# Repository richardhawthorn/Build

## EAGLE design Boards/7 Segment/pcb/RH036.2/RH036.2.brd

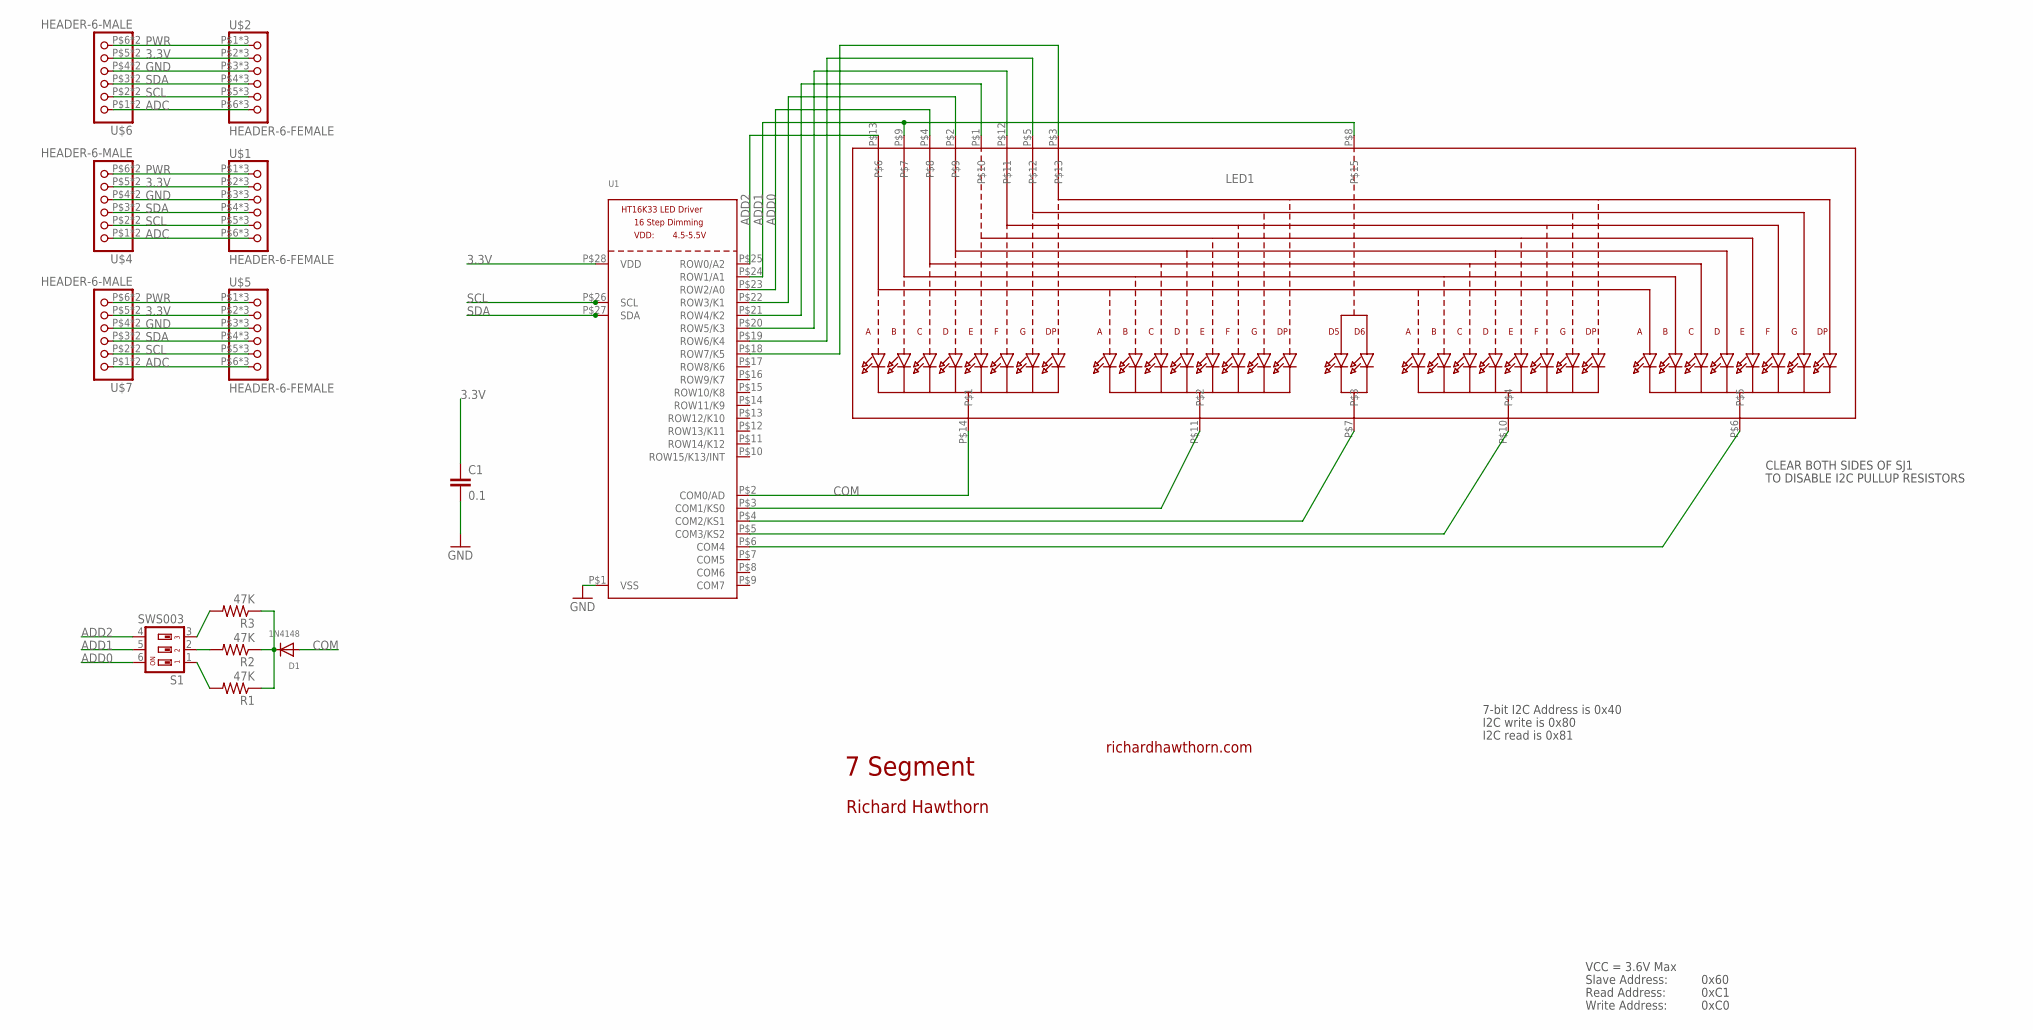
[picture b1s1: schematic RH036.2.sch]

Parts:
C1: 0.1; 0603-CAP
D1: 1N4148; SOD-323F
LED1: DISP_SEGMENT_4DIGIT_BL-Q56C43; SEGMENT-BL-Q56C43
R1, R2, R3: 47K; R0805
S1: SWS003; SMS-003
U1: HT16K33_SOP28; SOP28_300MIL
U$1, U$2, U$5: HEADER-6-FEMALE; 2MMHEADER6
U$4, U$6, U$7: HEADER-6-MALE; 2MMHEADERPIN6

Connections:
3.3V: C1.1, U1.P$28 (VDD), U$1.P$2 (2), U$1.P$10 (2), U$1.P$18 (2), U$2.P$2 (2), U$2.P$10 (2), U$2.P$18 (2), U$4.P$5 (5), U$4.P$13 (5), U$5.P$2 (2), U$5.P$10 (2), U$5.P$18 (2), U$6.P$5 (5), U$6.P$13 (5), U$7.P$5 (5), U$7.P$13 (5)
ADC: U$1.P$6 (6), U$1.P$14 (6), U$1.P$22 (6), U$2.P$6 (6), U$2.P$14 (6), U$2.P$22 (6), U$4.P$1 (1), U$4.P$9 (1), U$5.P$6 (6), U$5.P$14 (6), U$5.P$22 (6), U$6.P$1 (1), U$6.P$9 (1), U$7.P$1 (1), U$7.P$9 (1)
ADD0: LED1.P$4, S1.6, U1.P$23 (ROW2/A0)
ADD1: LED1.P$8, LED1.P$9, S1.5, U1.P$24 (ROW1/A1)
ADD2: LED1.P$13, S1.4, U1.P$25 (ROW0/A2)
COM: D1.A, LED1.P$14, U1.P$2 (COM0/AD)
GND: C1.2, U1.P$1 (VSS), U$1.P$3 (3), U$1.P$11 (3), U$1.P$19 (3), U$2.P$3 (3), U$2.P$11 (3), U$2.P$19 (3), U$4.P$4 (4), U$4.P$12 (4), U$5.P$3 (3), U$5.P$11 (3), U$5.P$19 (3), U$6.P$4 (4), U$6.P$12 (4), U$7.P$4 (4), U$7.P$12 (4)
unnamed: R3.2, S1.3
unnamed: LED1.P$11, U1.P$3 (COM1/KS0)
unnamed: LED1.P$7, U1.P$4 (COM2/KS1)
unnamed: LED1.P$10, U1.P$5 (COM3/KS2)
unnamed: LED1.P$6, U1.P$6 (COM4)
unnamed: LED1.P$2, U1.P$22 (ROW3/K1)
unnamed: LED1.P$1, U1.P$21 (ROW4/K2)
unnamed: LED1.P$12, U1.P$20 (ROW5/K3)
unnamed: LED1.P$5, U1.P$19 (ROW6/K4)
unnamed: LED1.P$3, U1.P$18 (ROW7/K5)
unnamed: D1.C, R1.1, R2.1, R3.1
unnamed: R1.2, S1.1
unnamed: R2.2, S1.2
PWR: U$1.P$1 (1), U$1.P$9 (1), U$1.P$17 (1), U$2.P$1 (1), U$2.P$9 (1), U$2.P$17 (1), U$4.P$6 (6), U$4.P$14 (6), U$5.P$1 (1), U$5.P$9 (1), U$5.P$17 (1), U$6.P$6 (6), U$6.P$14 (6), U$7.P$6 (6), U$7.P$14 (6)
SCL: U1.P$26 (SCL), U$1.P$5 (5), U$1.P$13 (5), U$1.P$21 (5), U$2.P$5 (5), U$2.P$13 (5), U$2.P$21 (5), U$4.P$2 (2), U$4.P$10 (2), U$5.P$5 (5), U$5.P$13 (5), U$5.P$21 (5), U$6.P$2 (2), U$6.P$10 (2), U$7.P$2 (2), U$7.P$10 (2)
SDA: U1.P$27 (SDA), U$1.P$4 (4), U$1.P$12 (4), U$1.P$20 (4), U$2.P$4 (4), U$2.P$12 (4), U$2.P$20 (4), U$4.P$3 (3), U$4.P$11 (3), U$5.P$4 (4), U$5.P$12 (4), U$5.P$20 (4), U$6.P$3 (3), U$6.P$11 (3), U$7.P$3 (3), U$7.P$11 (3)

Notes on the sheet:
7 Segment
richardhawthorn.com
Richard Hawthorn
CLEAR BOTH SIDES OF SJ1
TO DISABLE I2C PULLUP RESISTORS
7-bit I2C Address is 0x40
I2C write is 0x80
I2C read is 0x81
VCC = 3.6V Max
Read Address:
Write Address:
Slave Address:
0x60
0xC1
0xC0

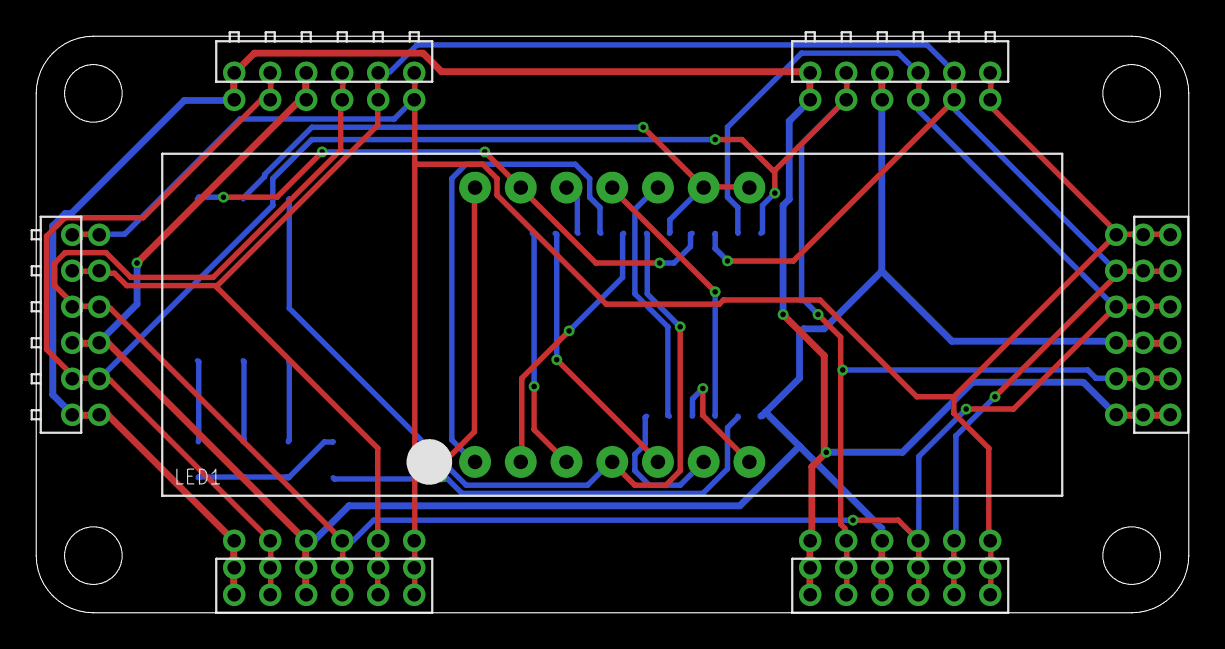
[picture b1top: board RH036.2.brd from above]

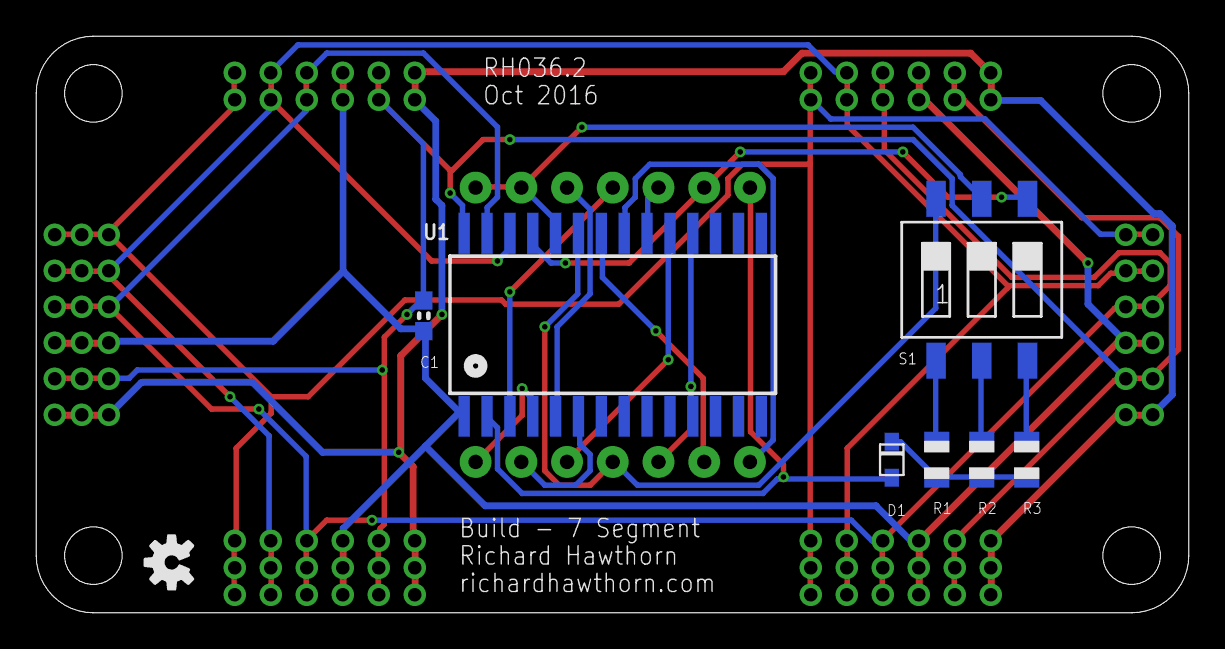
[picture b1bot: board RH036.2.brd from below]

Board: 2 copper layers, 64.0 x 32.0 mm, 15 parts (8 on the bottom side), 23 nets.

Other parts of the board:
U$3: OSHW-LOGO-S

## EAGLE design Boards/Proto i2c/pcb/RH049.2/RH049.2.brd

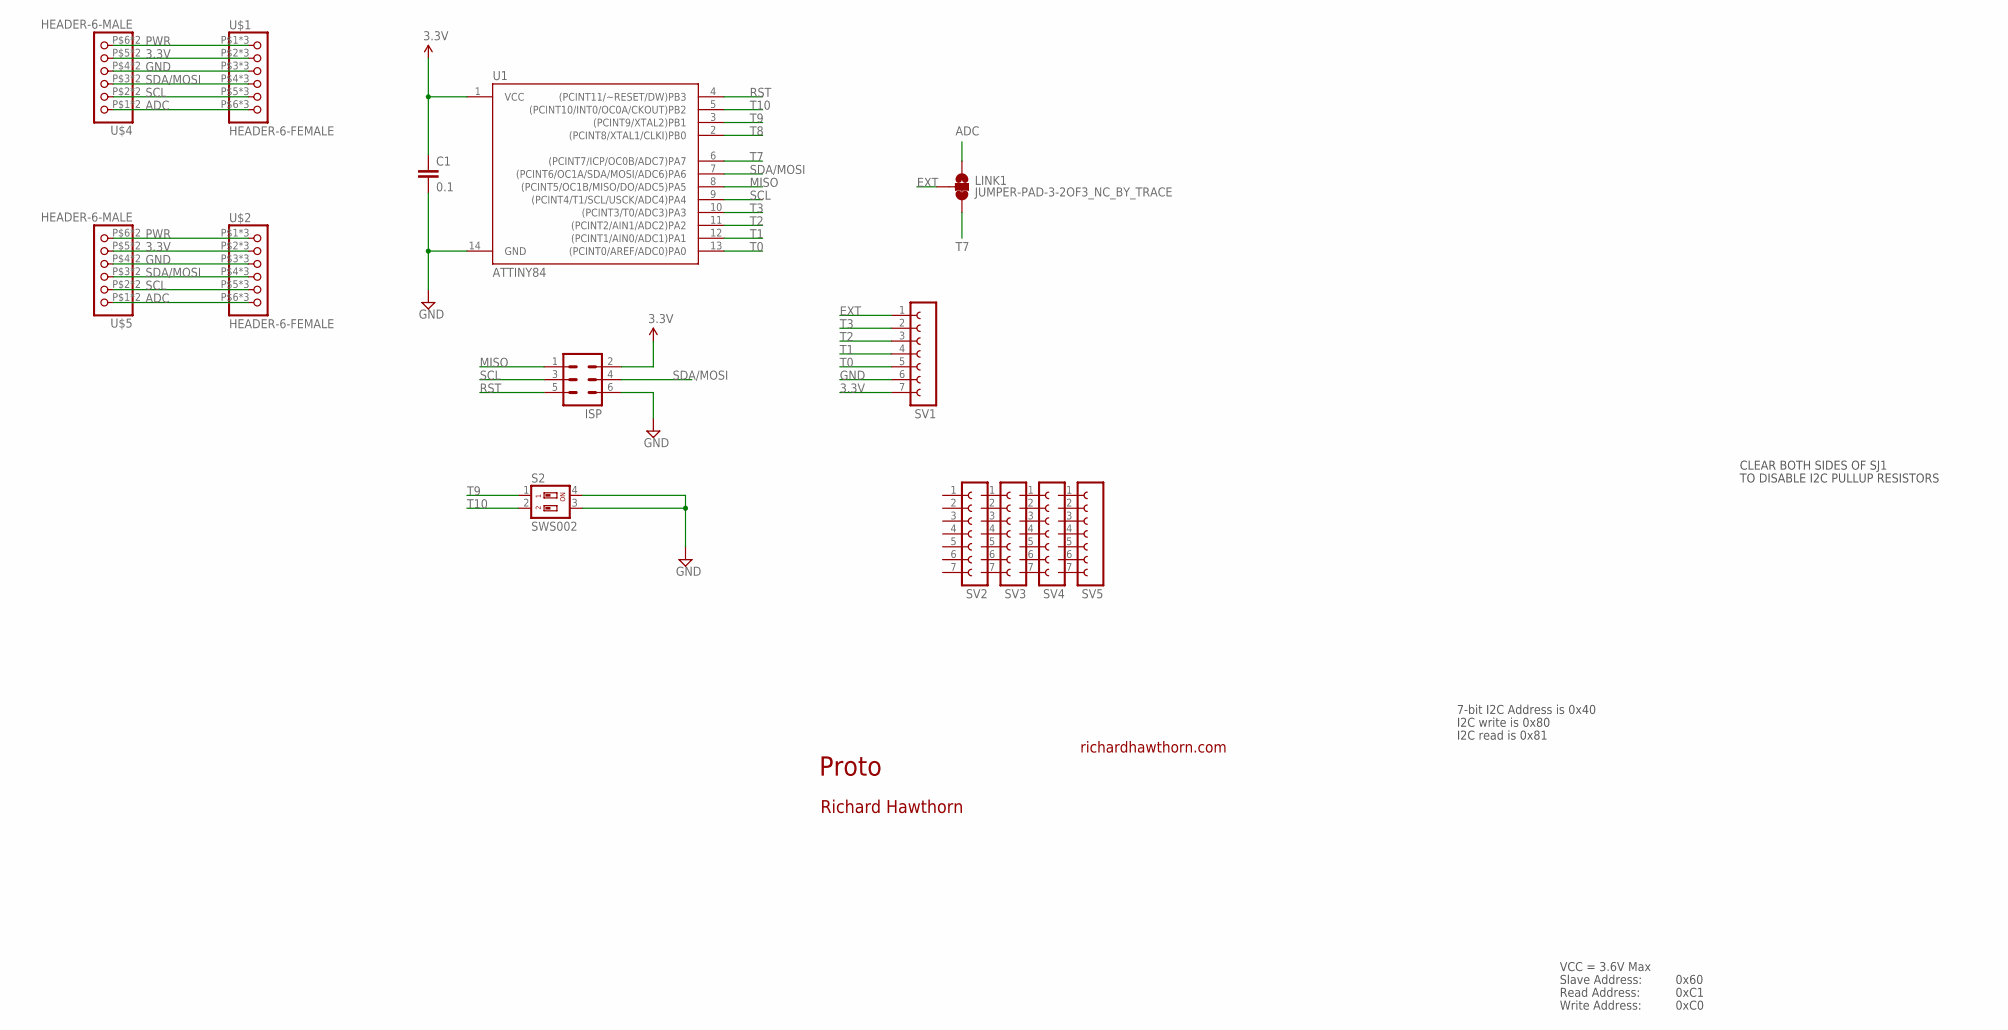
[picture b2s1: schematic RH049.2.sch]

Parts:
C1: 0.1; 0603-CAP
ISP: MA03-2
LINK1: JUMPER-PAD-3-2OF3_NC_BY_TRACE; PAD-JUMPER-3-2OF3_NC_BY_TRACE_YES_SILK_FULL_BOX
S2: SWS002; SMS-002
SV1, SV2, SV3, SV4, SV5: FE07-1; FE07
U1: ATTINY84; SO14
U$1, U$2: HEADER-6-FEMALE; 2MMHEADER6
U$4, U$5: HEADER-6-MALE; 2MMHEADERPIN6

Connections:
3.3V: C1.1, ISP.2, SV1.7, U1.1 (VCC), U$1.P$2 (2), U$1.P$10 (2), U$1.P$18 (2), U$2.P$2 (2), U$2.P$10 (2), U$2.P$18 (2), U$4.P$5 (5), U$4.P$13 (5), U$5.P$5 (5), U$5.P$13 (5)
ADC: LINK1.1, U$1.P$6 (6), U$1.P$14 (6), U$1.P$22 (6), U$2.P$6 (6), U$2.P$14 (6), U$2.P$22 (6), U$4.P$1 (1), U$4.P$9 (1), U$5.P$1 (1), U$5.P$9 (1)
EXT: LINK1.2, SV1.1
GND: C1.2, ISP.6, S2.3, S2.4, SV1.6, U1.14 (GND), U$1.P$3 (3), U$1.P$11 (3), U$1.P$19 (3), U$2.P$3 (3), U$2.P$11 (3), U$2.P$19 (3), U$4.P$4 (4), U$4.P$12 (4), U$5.P$4 (4), U$5.P$12 (4)
MISO: ISP.1, U1.8 ((PCINT5/OC1B/MISO/DO/ADC5)PA5)
PWR: U$1.P$1 (1), U$1.P$9 (1), U$1.P$17 (1), U$2.P$1 (1), U$2.P$9 (1), U$2.P$17 (1), U$4.P$6 (6), U$4.P$14 (6), U$5.P$6 (6), U$5.P$14 (6)
RST: ISP.5, U1.4 ((PCINT11/~RESET/DW)PB3)
SCL: ISP.3, U1.9 ((PCINT4/T1/SCL/USCK/ADC4)PA4), U$1.P$5 (5), U$1.P$13 (5), U$1.P$21 (5), U$2.P$5 (5), U$2.P$13 (5), U$2.P$21 (5), U$4.P$2 (2), U$4.P$10 (2), U$5.P$2 (2), U$5.P$10 (2)
SDA/MOSI: ISP.4, U1.7 ((PCINT6/OC1A/SDA/MOSI/ADC6)PA6), U$1.P$4 (4), U$1.P$12 (4), U$1.P$20 (4), U$2.P$4 (4), U$2.P$12 (4), U$2.P$20 (4), U$4.P$3 (3), U$4.P$11 (3), U$5.P$3 (3), U$5.P$11 (3)
T0: SV1.5, U1.13 ((PCINT0/AREF/ADC0)PA0)
T1: SV1.4, U1.12 ((PCINT1/AIN0/ADC1)PA1)
T2: SV1.3, U1.11 ((PCINT2/AIN1/ADC2)PA2)
T3: SV1.2, U1.10 ((PCINT3/T0/ADC3)PA3)
T7: LINK1.3, U1.6 ((PCINT7/ICP/OC0B/ADC7)PA7)
T8: U1.2 ((PCINT8/XTAL1/CLKI)PB0)
T9: S2.1, U1.3 ((PCINT9/XTAL2)PB1)
T10: S2.2, U1.5 ((PCINT10/INT0/OC0A/CKOUT)PB2)

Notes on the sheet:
Proto
richardhawthorn.com
Richard Hawthorn
CLEAR BOTH SIDES OF SJ1
TO DISABLE I2C PULLUP RESISTORS
7-bit I2C Address is 0x40
I2C write is 0x80
I2C read is 0x81
VCC = 3.6V Max
Read Address:
Write Address:
Slave Address:
0x60
0xC1
0xC0

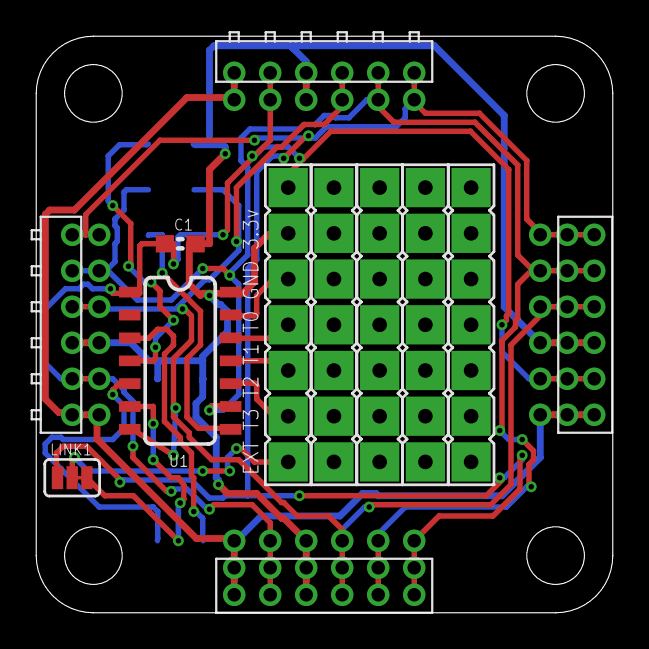
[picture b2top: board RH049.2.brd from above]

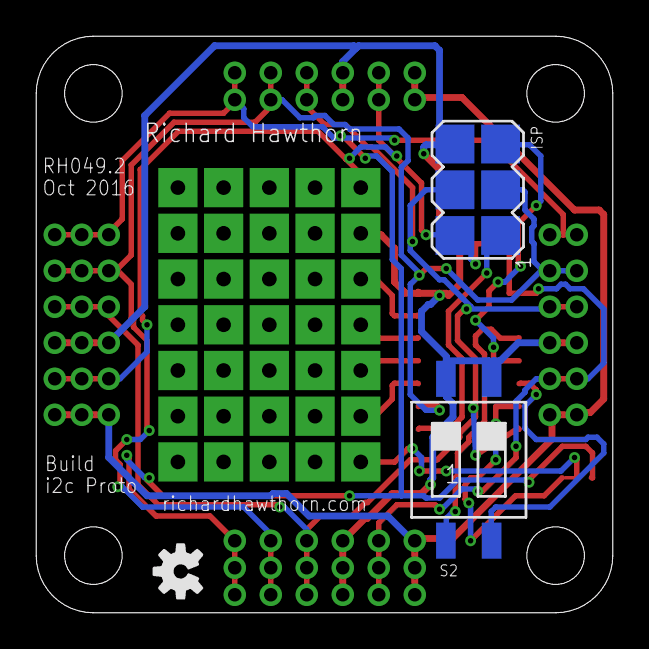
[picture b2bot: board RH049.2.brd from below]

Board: 2 copper layers, 32.0 x 32.0 mm, 15 parts (3 on the bottom side), 16 nets.

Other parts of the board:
U$3: OSHW-LOGO-S

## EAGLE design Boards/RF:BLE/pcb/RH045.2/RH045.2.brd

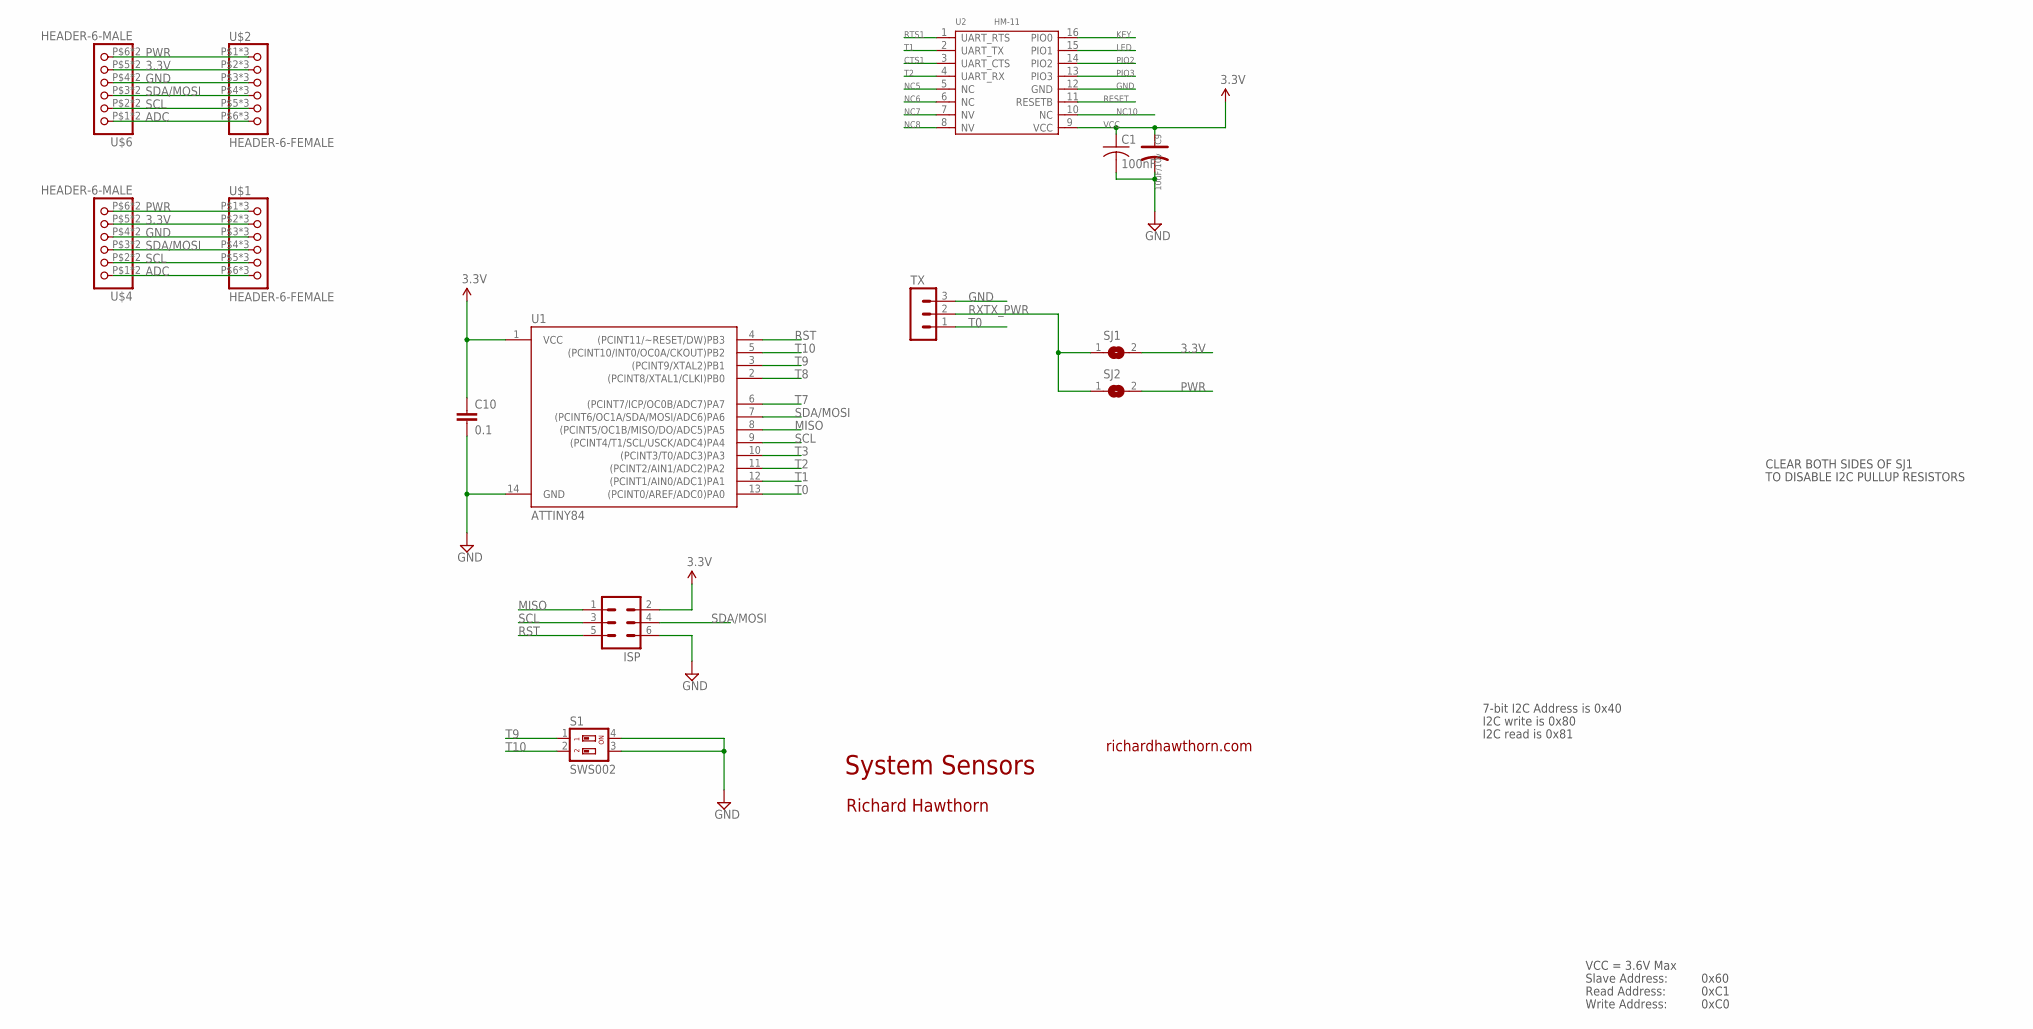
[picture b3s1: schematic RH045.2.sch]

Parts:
C1: 100nF; C0805
C9: 10uF/10v; AVX-A
C10: 0.1; 0603-CAP
ISP: MA03-2
S1: SWS002; SMS-002
SJ1, SJ2: SJ
TX: MA03-1
U1: ATTINY84; SO14
U2: HM-11; 16P-18.5X13.5X0.8
U$1, U$2: HEADER-6-FEMALE; 2MMHEADER6
U$4, U$6: HEADER-6-MALE; 2MMHEADERPIN6

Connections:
3.3V: C10.1, ISP.2, SJ1.2, U1.1 (VCC), U$1.P$2 (2), U$1.P$10 (2), U$1.P$18 (2), U$2.P$2 (2), U$2.P$10 (2), U$2.P$18 (2), U$4.P$5 (5), U$4.P$13 (5), U$6.P$5 (5), U$6.P$13 (5)
ADC: U$1.P$6 (6), U$1.P$14 (6), U$1.P$22 (6), U$2.P$6 (6), U$2.P$14 (6), U$2.P$22 (6), U$4.P$1 (1), U$4.P$9 (1), U$6.P$1 (1), U$6.P$9 (1)
CTS1: U2.3 (UART_CTS)
GND: C1.2, C9.-, C10.2, ISP.6, S1.3, S1.4, TX.3, U1.14 (GND), U2.12 (GND), U$1.P$3 (3), U$1.P$11 (3), U$1.P$19 (3), U$2.P$3 (3), U$2.P$11 (3), U$2.P$19 (3), U$4.P$4 (4), U$4.P$12 (4), U$6.P$4 (4), U$6.P$12 (4)
KEY: U2.16 (PIO0)
LED: U2.15 (PIO1)
MISO: ISP.1, U1.8 ((PCINT5/OC1B/MISO/DO/ADC5)PA5)
NC5: U2.5 (NC)
NC6: U2.6 (NC)
NC7: U2.7 (NV)
NC8: U2.8 (NV)
NC10: U2.10 (NC)
PIO2: U2.14 (PIO2)
PIO3: U2.13 (PIO3)
PWR: SJ2.2, U$1.P$1 (1), U$1.P$9 (1), U$1.P$17 (1), U$2.P$1 (1), U$2.P$9 (1), U$2.P$17 (1), U$4.P$6 (6), U$4.P$14 (6), U$6.P$6 (6), U$6.P$14 (6)
RESET: U2.11 (RESETB)
RST: ISP.5, U1.4 ((PCINT11/~RESET/DW)PB3)
RTS1: U2.1 (UART_RTS)
RXTX_PWR: SJ1.1, SJ2.1, TX.2
SCL: ISP.3, U1.9 ((PCINT4/T1/SCL/USCK/ADC4)PA4), U$1.P$5 (5), U$1.P$13 (5), U$1.P$21 (5), U$2.P$5 (5), U$2.P$13 (5), U$2.P$21 (5), U$4.P$2 (2), U$4.P$10 (2), U$6.P$2 (2), U$6.P$10 (2)
SDA/MOSI: ISP.4, U1.7 ((PCINT6/OC1A/SDA/MOSI/ADC6)PA6), U$1.P$4 (4), U$1.P$12 (4), U$1.P$20 (4), U$2.P$4 (4), U$2.P$12 (4), U$2.P$20 (4), U$4.P$3 (3), U$4.P$11 (3), U$6.P$3 (3), U$6.P$11 (3)
T0: TX.1, U1.13 ((PCINT0/AREF/ADC0)PA0)
T1: U1.12 ((PCINT1/AIN0/ADC1)PA1), U2.2 (UART_TX)
T2: U1.11 ((PCINT2/AIN1/ADC2)PA2), U2.4 (UART_RX)
T3: U1.10 ((PCINT3/T0/ADC3)PA3)
T7: U1.6 ((PCINT7/ICP/OC0B/ADC7)PA7)
T8: U1.2 ((PCINT8/XTAL1/CLKI)PB0)
T9: S1.1, U1.3 ((PCINT9/XTAL2)PB1)
T10: S1.2, U1.5 ((PCINT10/INT0/OC0A/CKOUT)PB2)
VCC: C1.1, C9.+, U2.9 (VCC)

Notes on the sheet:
System Sensors
richardhawthorn.com
Richard Hawthorn
CLEAR BOTH SIDES OF SJ1
TO DISABLE I2C PULLUP RESISTORS
7-bit I2C Address is 0x40
I2C write is 0x80
I2C read is 0x81
VCC = 3.6V Max
Read Address:
Write Address:
Slave Address:
0x60
0xC1
0xC0

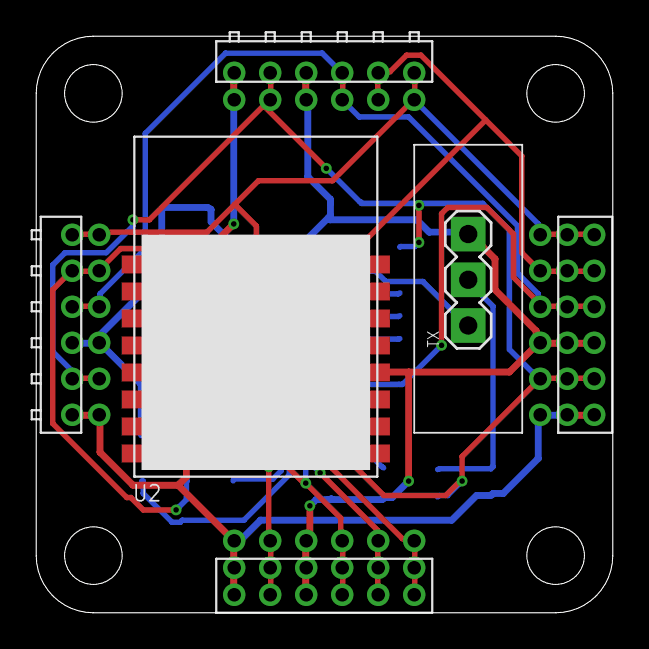
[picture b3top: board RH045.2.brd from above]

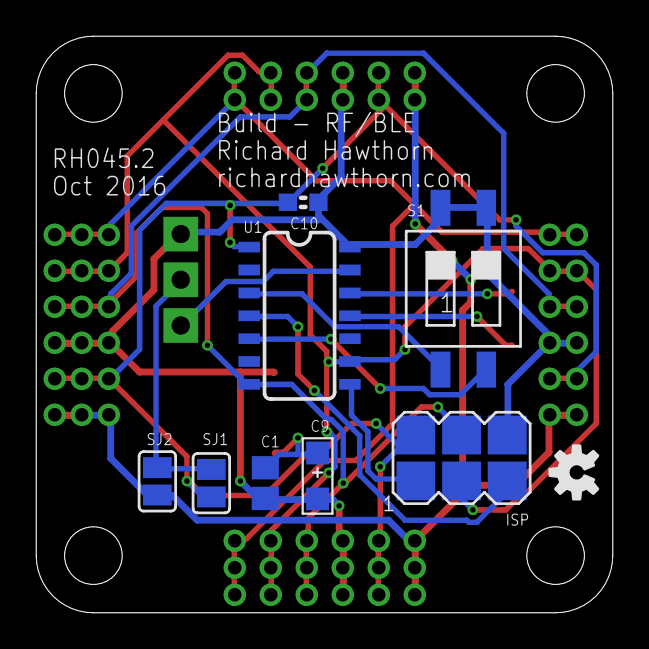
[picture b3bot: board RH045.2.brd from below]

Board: 2 copper layers, 32.0 x 32.0 mm, 15 parts (9 on the bottom side), 15 nets.

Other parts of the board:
U$3: OSHW-LOGO-S

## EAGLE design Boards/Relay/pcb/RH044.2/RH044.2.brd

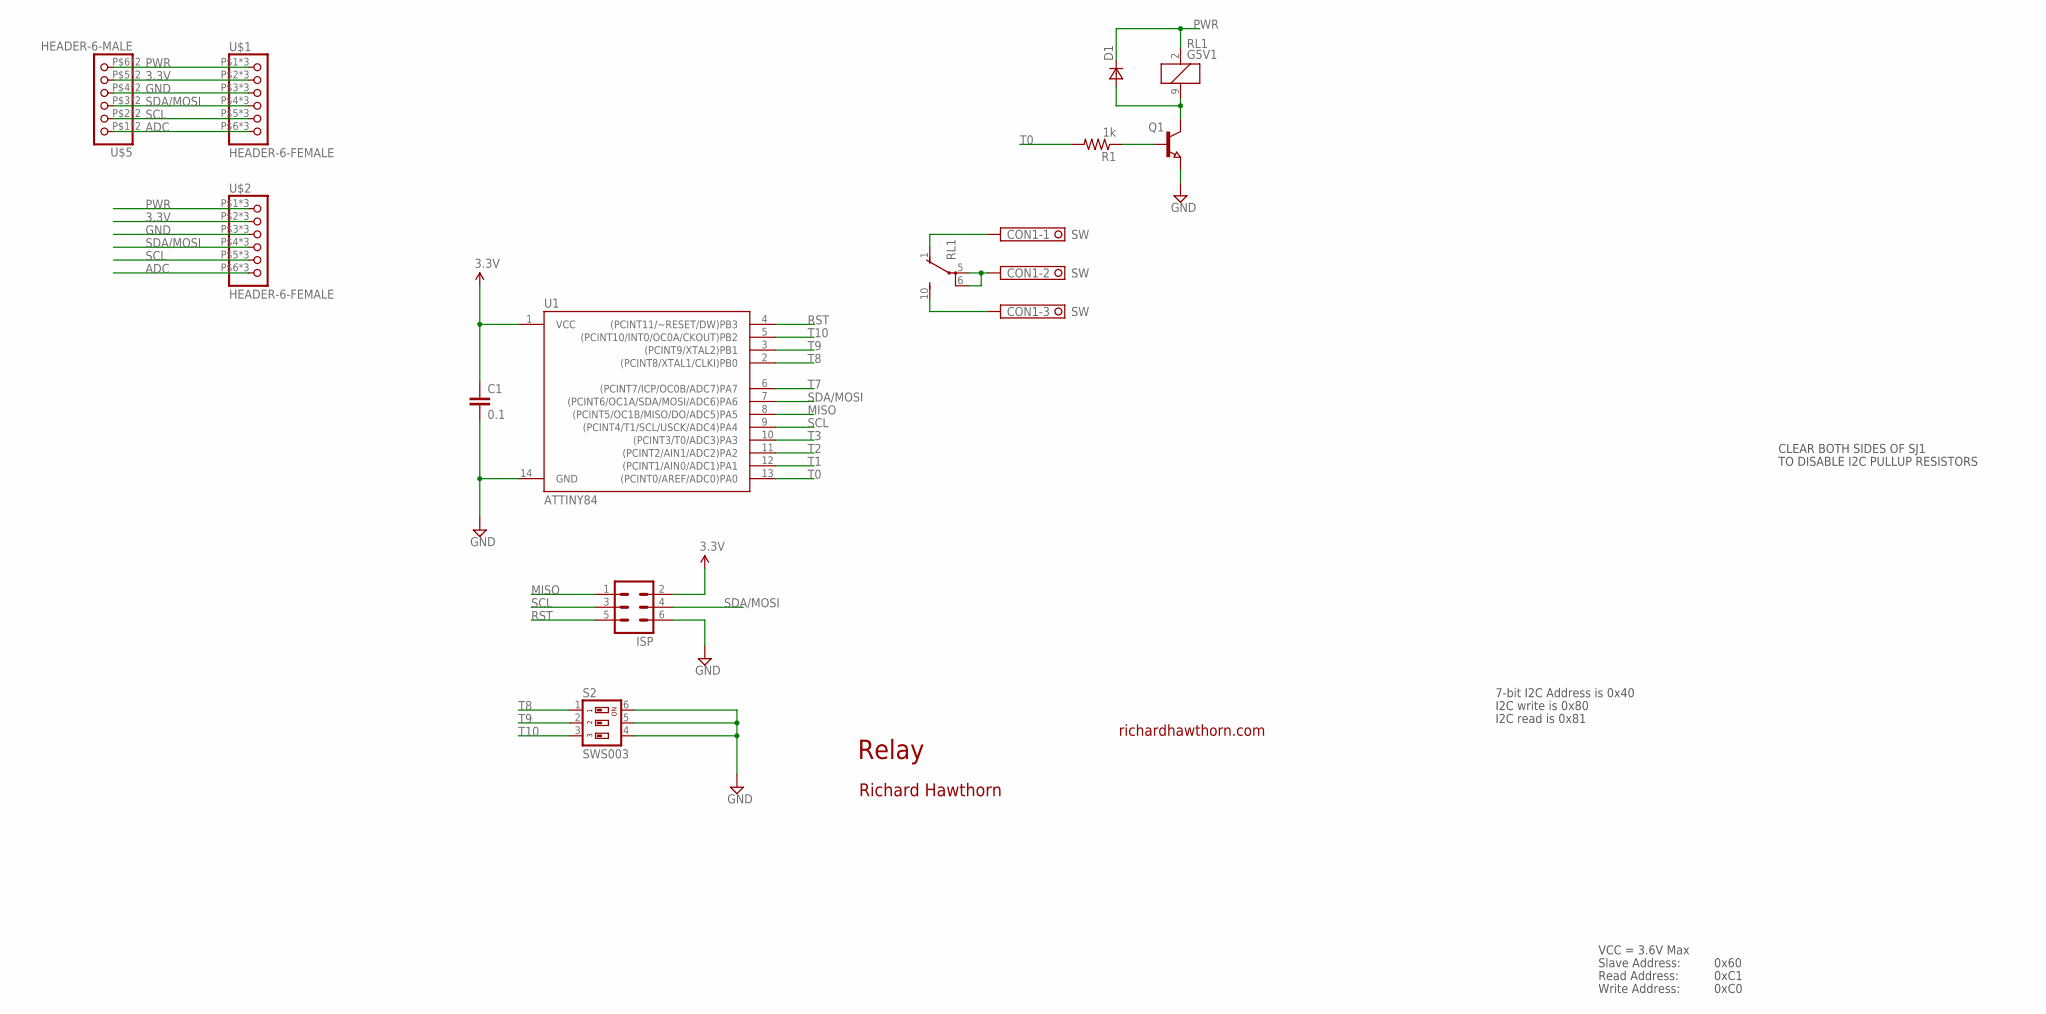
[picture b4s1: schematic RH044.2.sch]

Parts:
C1: 0.1; 0603-CAP
CON1: SW; 1751251
D1: VAR2SOT23; SOT-23
ISP: MA03-2
Q1: NPN-TRANSISTOR_SOT23; SOT23
R1: 1k; 0603-RES
RL1: G5V1
S2: SWS003; SMS-003
U1: ATTINY84; SO14
U$1, U$2: HEADER-6-FEMALE; 2MMHEADER6
U$5: HEADER-6-MALE; 2MMHEADERPIN6

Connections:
3.3V: C1.1, ISP.2, U1.1 (VCC), U$1.P$2 (2), U$1.P$10 (2), U$1.P$18 (2), U$2.P$2 (2), U$2.P$10 (2), U$2.P$18 (2), U$5.P$5 (5), U$5.P$13 (5)
ADC: U$1.P$6 (6), U$1.P$14 (6), U$1.P$22 (6), U$2.P$6 (6), U$2.P$14 (6), U$2.P$22 (6), U$5.P$1 (1), U$5.P$9 (1)
COM: CON1.2, RL1.5, RL1.6
GND: C1.2, ISP.6, Q1.2 (E), S2.4, S2.5, S2.6, U1.14 (GND), U$1.P$3 (3), U$1.P$11 (3), U$1.P$19 (3), U$2.P$3 (3), U$2.P$11 (3), U$2.P$19 (3), U$5.P$4 (4), U$5.P$12 (4)
MISO: ISP.1, U1.8 ((PCINT5/OC1B/MISO/DO/ADC5)PA5)
unnamed: Q1.1 (B), R1.1
unnamed: D1.3 (A), Q1.3 (C), RL1.9 (2)
NC: CON1.1, RL1.1 (O)
NO: CON1.3, RL1.10 (S)
PWR: D1.1 (C), RL1.2 (1), U$1.P$1 (1), U$1.P$9 (1), U$1.P$17 (1), U$2.P$1 (1), U$2.P$9 (1), U$2.P$17 (1), U$5.P$6 (6), U$5.P$14 (6)
RST: ISP.5, U1.4 ((PCINT11/~RESET/DW)PB3)
SCL: ISP.3, U1.9 ((PCINT4/T1/SCL/USCK/ADC4)PA4), U$1.P$5 (5), U$1.P$13 (5), U$1.P$21 (5), U$2.P$5 (5), U$2.P$13 (5), U$2.P$21 (5), U$5.P$2 (2), U$5.P$10 (2)
SDA/MOSI: ISP.4, U1.7 ((PCINT6/OC1A/SDA/MOSI/ADC6)PA6), U$1.P$4 (4), U$1.P$12 (4), U$1.P$20 (4), U$2.P$4 (4), U$2.P$12 (4), U$2.P$20 (4), U$5.P$3 (3), U$5.P$11 (3)
T0: R1.2, U1.13 ((PCINT0/AREF/ADC0)PA0)
T1: U1.12 ((PCINT1/AIN0/ADC1)PA1)
T2: U1.11 ((PCINT2/AIN1/ADC2)PA2)
T3: U1.10 ((PCINT3/T0/ADC3)PA3)
T7: U1.6 ((PCINT7/ICP/OC0B/ADC7)PA7)
T8: S2.1, U1.2 ((PCINT8/XTAL1/CLKI)PB0)
T9: S2.2, U1.3 ((PCINT9/XTAL2)PB1)
T10: S2.3, U1.5 ((PCINT10/INT0/OC0A/CKOUT)PB2)

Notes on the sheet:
Relay
richardhawthorn.com
Richard Hawthorn
CLEAR BOTH SIDES OF SJ1
TO DISABLE I2C PULLUP RESISTORS
7-bit I2C Address is 0x40
I2C write is 0x80
I2C read is 0x81
VCC = 3.6V Max
Read Address:
Write Address:
Slave Address:
0x60
0xC1
0xC0

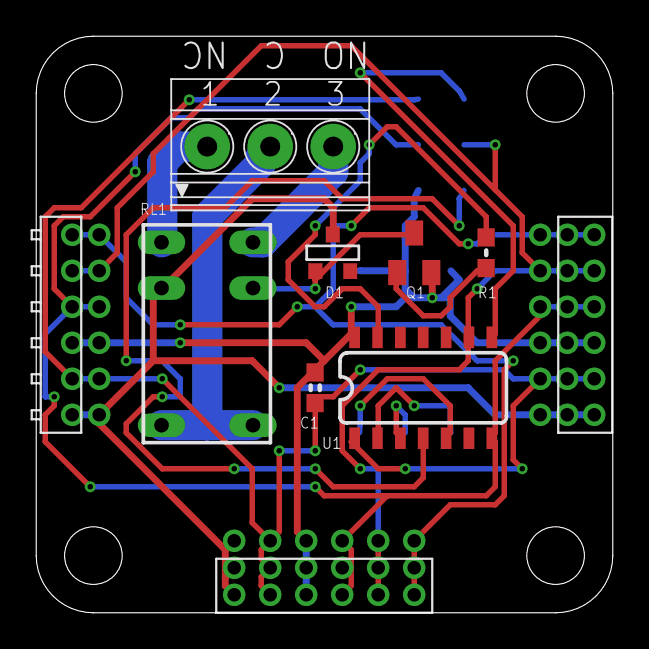
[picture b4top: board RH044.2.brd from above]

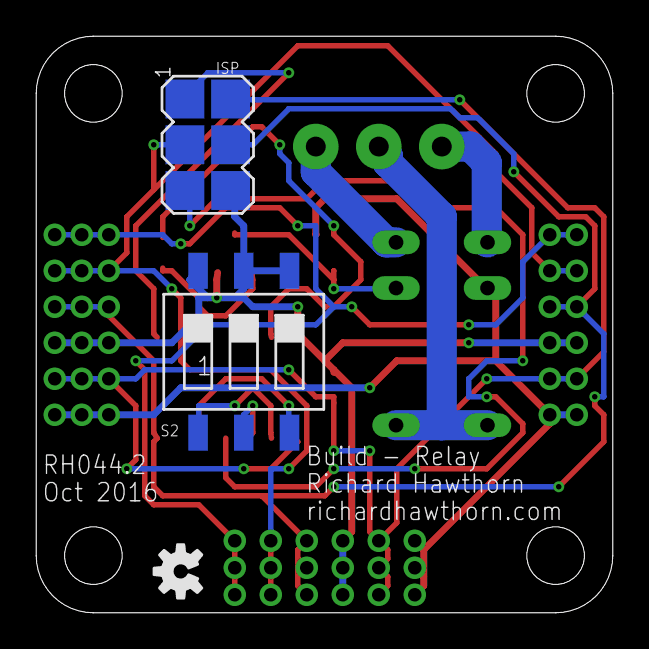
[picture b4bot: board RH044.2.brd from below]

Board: 2 copper layers, 32.0 x 32.0 mm, 13 parts (3 on the bottom side), 17 nets.

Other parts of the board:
U$3: OSHW-LOGO-S

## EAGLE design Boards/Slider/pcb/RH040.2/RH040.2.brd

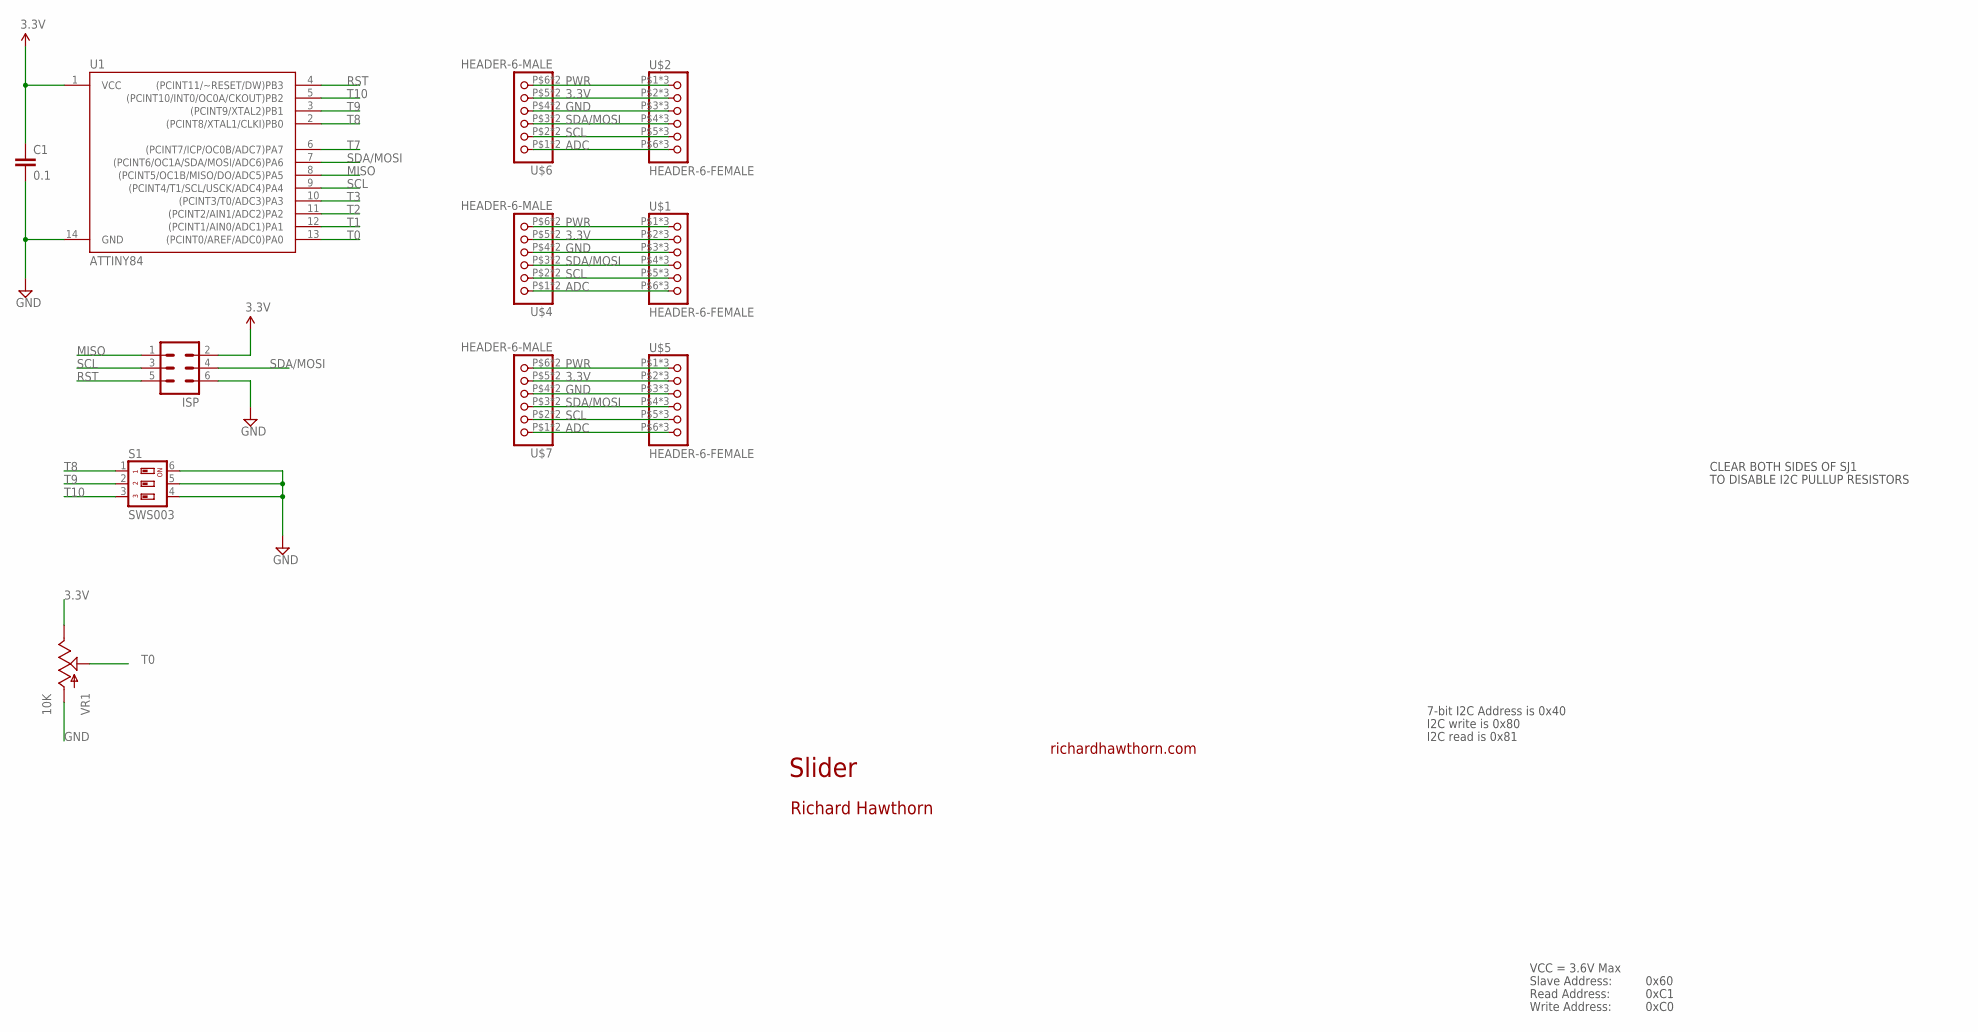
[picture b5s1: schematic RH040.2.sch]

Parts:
C1: 0.1; 0603-CAP
ISP: MA03-2
S1: SWS003; SMS-003
U1: ATTINY84; SO14
U$1, U$2, U$5: HEADER-6-FEMALE; 2MMHEADER6
U$4, U$6, U$7: HEADER-6-MALE; 2MMHEADERPIN6
VR1: 10K; SLIDER-MEDIUM-KIT

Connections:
3.3V: C1.1, ISP.2, U1.1 (VCC), U$1.P$2 (2), U$1.P$10 (2), U$1.P$18 (2), U$2.P$2 (2), U$2.P$10 (2), U$2.P$18 (2), U$4.P$5 (5), U$4.P$13 (5), U$5.P$2 (2), U$5.P$10 (2), U$5.P$18 (2), U$6.P$5 (5), U$6.P$13 (5), U$7.P$5 (5), U$7.P$13 (5), VR1.TOP (E)
ADC: U$1.P$6 (6), U$1.P$14 (6), U$1.P$22 (6), U$2.P$6 (6), U$2.P$14 (6), U$2.P$22 (6), U$4.P$1 (1), U$4.P$9 (1), U$5.P$6 (6), U$5.P$14 (6), U$5.P$22 (6), U$6.P$1 (1), U$6.P$9 (1), U$7.P$1 (1), U$7.P$9 (1)
GND: C1.2, ISP.6, S1.4, S1.5, S1.6, U1.14 (GND), U$1.P$3 (3), U$1.P$11 (3), U$1.P$19 (3), U$2.P$3 (3), U$2.P$11 (3), U$2.P$19 (3), U$4.P$4 (4), U$4.P$12 (4), U$5.P$3 (3), U$5.P$11 (3), U$5.P$19 (3), U$6.P$4 (4), U$6.P$12 (4), U$7.P$4 (4), U$7.P$12 (4), VR1.BOTTOM (A)
MISO: ISP.1, U1.8 ((PCINT5/OC1B/MISO/DO/ADC5)PA5)
PWR: U$1.P$1 (1), U$1.P$9 (1), U$1.P$17 (1), U$2.P$1 (1), U$2.P$9 (1), U$2.P$17 (1), U$4.P$6 (6), U$4.P$14 (6), U$5.P$1 (1), U$5.P$9 (1), U$5.P$17 (1), U$6.P$6 (6), U$6.P$14 (6), U$7.P$6 (6), U$7.P$14 (6)
RST: ISP.5, U1.4 ((PCINT11/~RESET/DW)PB3)
SCL: ISP.3, U1.9 ((PCINT4/T1/SCL/USCK/ADC4)PA4), U$1.P$5 (5), U$1.P$13 (5), U$1.P$21 (5), U$2.P$5 (5), U$2.P$13 (5), U$2.P$21 (5), U$4.P$2 (2), U$4.P$10 (2), U$5.P$5 (5), U$5.P$13 (5), U$5.P$21 (5), U$6.P$2 (2), U$6.P$10 (2), U$7.P$2 (2), U$7.P$10 (2)
SDA/MOSI: ISP.4, U1.7 ((PCINT6/OC1A/SDA/MOSI/ADC6)PA6), U$1.P$4 (4), U$1.P$12 (4), U$1.P$20 (4), U$2.P$4 (4), U$2.P$12 (4), U$2.P$20 (4), U$4.P$3 (3), U$4.P$11 (3), U$5.P$4 (4), U$5.P$12 (4), U$5.P$20 (4), U$6.P$3 (3), U$6.P$11 (3), U$7.P$3 (3), U$7.P$11 (3)
T0: U1.13 ((PCINT0/AREF/ADC0)PA0), VR1.WIPER (S)
T1: U1.12 ((PCINT1/AIN0/ADC1)PA1)
T2: U1.11 ((PCINT2/AIN1/ADC2)PA2)
T3: U1.10 ((PCINT3/T0/ADC3)PA3)
T7: U1.6 ((PCINT7/ICP/OC0B/ADC7)PA7)
T8: S1.1, U1.2 ((PCINT8/XTAL1/CLKI)PB0)
T9: S1.2, U1.3 ((PCINT9/XTAL2)PB1)
T10: S1.3, U1.5 ((PCINT10/INT0/OC0A/CKOUT)PB2)

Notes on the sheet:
Slider
richardhawthorn.com
Richard Hawthorn
CLEAR BOTH SIDES OF SJ1
TO DISABLE I2C PULLUP RESISTORS
7-bit I2C Address is 0x40
I2C write is 0x80
I2C read is 0x81
VCC = 3.6V Max
Read Address:
Write Address:
Slave Address:
0x60
0xC1
0xC0

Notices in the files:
parts and their libraries:
SparkFun-Aesthetics: Licensing: CC v3.0 Share-Alike You are welcome to use this library for commercial purposes.
SparkFun-DigitalIC: Licensing: Creative Commons ShareAlike 4.0 International - https://creativecommons.org/licenses/by-sa/4.0
